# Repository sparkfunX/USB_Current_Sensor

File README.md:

SparkX USB Current Sensor
========================================

[*SparkX USB Current Sensor (SPX-18016)*](https://www.sparkfun.com/products/17729)

Do you want to be able to measure what current your board is drawing in real time? Maybe it is a board that draws short bursts of current?
Or maybe you want to investigate what in-rush current your board draws? If so, this is the product for you!

The TI INA290 is an ultra-precise current sense amplifier that can measure voltage drops across shunt resistors over a wide common-mode range.
The INA290A1 on our board has a gain of 20 Volts per Volt and we measure the current using a 0.05 Ohm shunt resistor. Together these produce an
output of 1 Volt per Amp. If your board is drawing 100mA, you will see an output of 100mV. The maximum current it can measure is 2 Amps
and we've included a 2A resettable fuse for added protection.

We've provided both 0.1" breakout pads and Gator pads, to make it easy to connect up your multimeter or oscilloscope.
Feed power in via the USB-C socket, and provide power to your board via the USB-A socket.
A pair of [USB 2.0 A to C Cables](https://www.sparkfun.com/products/15092) will allow you to connect the input to your USB port or power supply
and the output to your board.
You might find our [BNC to Alligator Cable](https://www.sparkfun.com/products/504) useful for connecting to your oscilloscope.
Our [Banana to Alligator Coax Cable](https://www.sparkfun.com/products/508) is perfect for connecting your multimeter.

Repository Contents
-------------------
* **/Documents** - datasheets etc.
* **/Hardware** - Eagle design files (.brd, .sch)

Product Versions
----------------
* [SPX-18016](https://www.sparkfun.com/products/18016) - Original SparkX Release.

License Information
-------------------

This product is _**open source**_!

Please review the LICENSE.md file for license information.

If you have any questions or concerns on licensing, please contact technical support on our [SparkFun forums](https://forum.sparkfun.com/viewforum.php?f=152).

Distributed as-is; no warranty is given.

- Your friends at SparkFun.

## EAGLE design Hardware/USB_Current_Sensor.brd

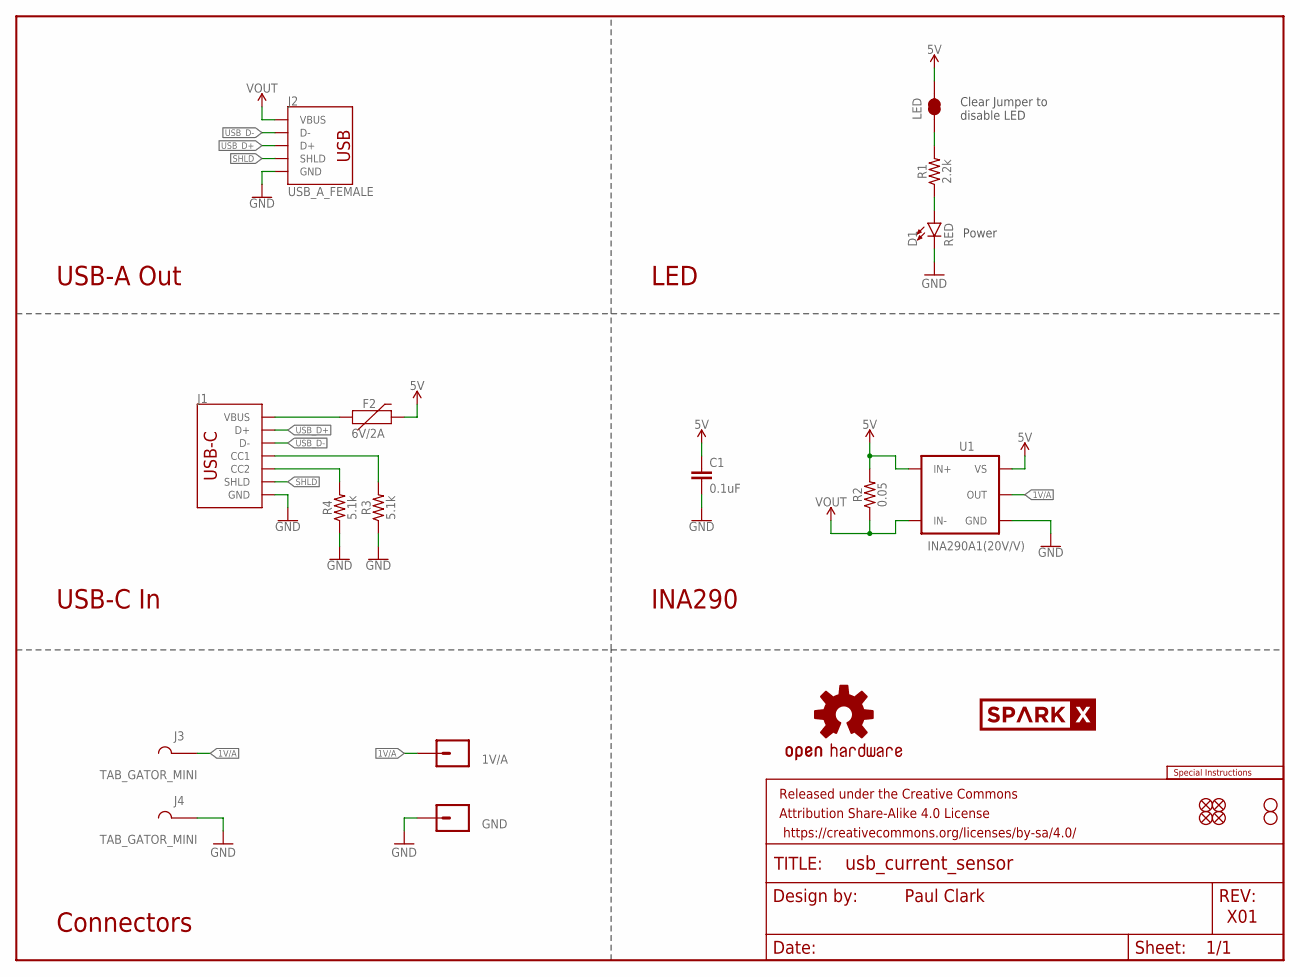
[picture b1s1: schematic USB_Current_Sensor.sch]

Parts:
1V/A: CONN_01PTH_NO_SILK_YES_STOP; 1X01_NO_SILK
C1: 0.1uF; 0603
D1: RED; LED-0603
F2: 6V/2A; 1210
FRAME1: FRAME-LETTER; CREATIVE_COMMONS
GND: CONN_01PTH_NO_SILK_YES_STOP; 1X01_NO_SILK
J1: USB_C_4-LAYER_PADS; USB-C-16P_4LAYER-PADS
J2: USB_A_FEMALE; USB-A-S-NOSILK-FEMALE
J3, J4: TAB_GATOR_MINI
JP1, JP2, JP5, JP6: FIDUCIAL1X2; FIDUCIAL-1X2
JP3, JP4: STAND-OFF
LED: JUMPER-SMT_2_NC_TRACE_SILK; SMT-JUMPER_2_NC_TRACE_SILK
LOGO1: OSHW-LOGOMINI; OSHW-LOGO-MINI
LOGO2: SPECIAL_INSTRUCTIONS-ORDERING; ORDERING_INSTRUCTIONS
R1: 2.2k; 0603
R2: 0.05; 0603
R3, R4: 5.1k; 0603
U1: INA290A1(20V/V); SC70
U$2: SPARKX-LOGO4; SPARKX-MEDIUM

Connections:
1V/A: 1V/A.1, J3.P1, U1.1 (OUT)
5V: C1.1, F2.2, LED.2, R2.2, U1.3 (VS), U1.4 (IN+)
GND: C1.2, D1.C, GND.1, J1.GND, J1.GND2 (GND), J2.GND, J4.P1, R3.1, R4.1, U1.2 (GND)
unnamed: D1.A, R1.1
unnamed: LED.1, R1.2
unnamed: J1.A5 (CC1), R3.2
unnamed: J1.B5 (CC2), R4.2
unnamed: F2.1, J1.VBUS1 (VBUS), J1.VBUS2 (VBUS)
SHLD: J1.SHLD1 (SHLD), J1.SHLD2 (SHLD), J1.SHLD3 (SHLD), J1.SHLD4 (SHLD), J2.SHLD1 (SHLD), J2.SHLD2 (SHLD)
USB_D+: J1.A6 (D+), J1.B6 (D+), J2.D+
USB_D-: J1.A7 (D-), J1.B7 (D-), J2.D-
VOUT: J2.VBUS, R2.1, U1.5 (IN-)

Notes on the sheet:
Paul Clark
X01
Power
Connectors
Clear Jumper to disable LED
LED
INA290
USB-C In
USB-A Out

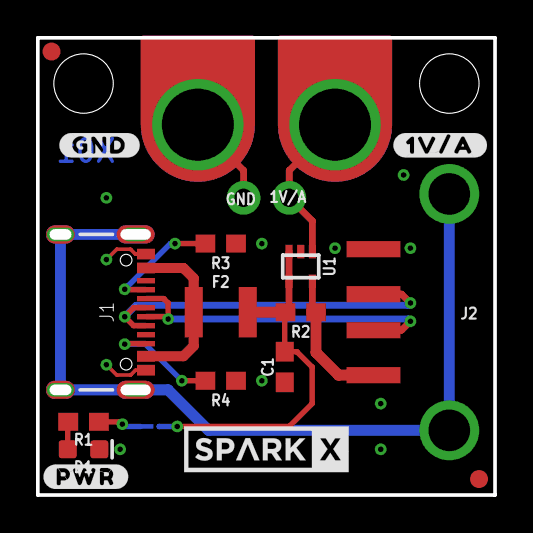
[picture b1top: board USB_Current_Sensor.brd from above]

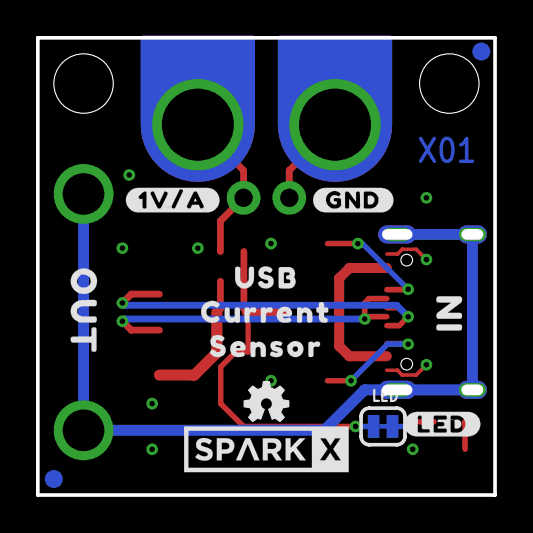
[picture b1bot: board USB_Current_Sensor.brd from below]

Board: 2 copper layers, 25.4 x 25.4 mm, 37 parts (13 on the bottom side), 12 nets.

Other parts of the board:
U$1: SPARKX-LOGO4; SPARKX-MEDIUM
U$3, U$4: #GND#0
U$5, U$6: #1V#A#0
U$7: USB0
U$8: CURRENT0
U$9: SENSOR0
U$10: IN0
U$11: OUT0
U$13: #PWR#0
U$14: #LED#0

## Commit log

2021-02-20 Adding production files
2021-02-26 Correcting the PROD_ID

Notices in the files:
parts and their libraries:
SparkFun-Resistors: Licensing: Creative Commons ShareAlike 4.0 International - https://creativecommons.org/licenses/by-sa/4.0
SparkFun-Aesthetics: Released under the Creative Commons Attribution Share-Alike 4.0 License
SparkFun-Aesthetics: https://creativecommons.org/licenses/by-sa/4.0
